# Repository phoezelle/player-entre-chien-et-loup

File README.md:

# player-entre-chien-et-loup
audio player for urban ballad http://www.cie-entrechienetloup.net/spectacles/verena-velvet.htm

The audio player work with 1 dedicated electronic card (cf pcb folder)
use atmega 328, vlsi vs1033/53, nordic NRF24L01+

You can control the system with a dedicated remote (cf pcb folder)
use atmega 328, hc595, nordic NRF24L01+, sparkfun LCD, keypad (optional)

use like arduino library
Player
Remote

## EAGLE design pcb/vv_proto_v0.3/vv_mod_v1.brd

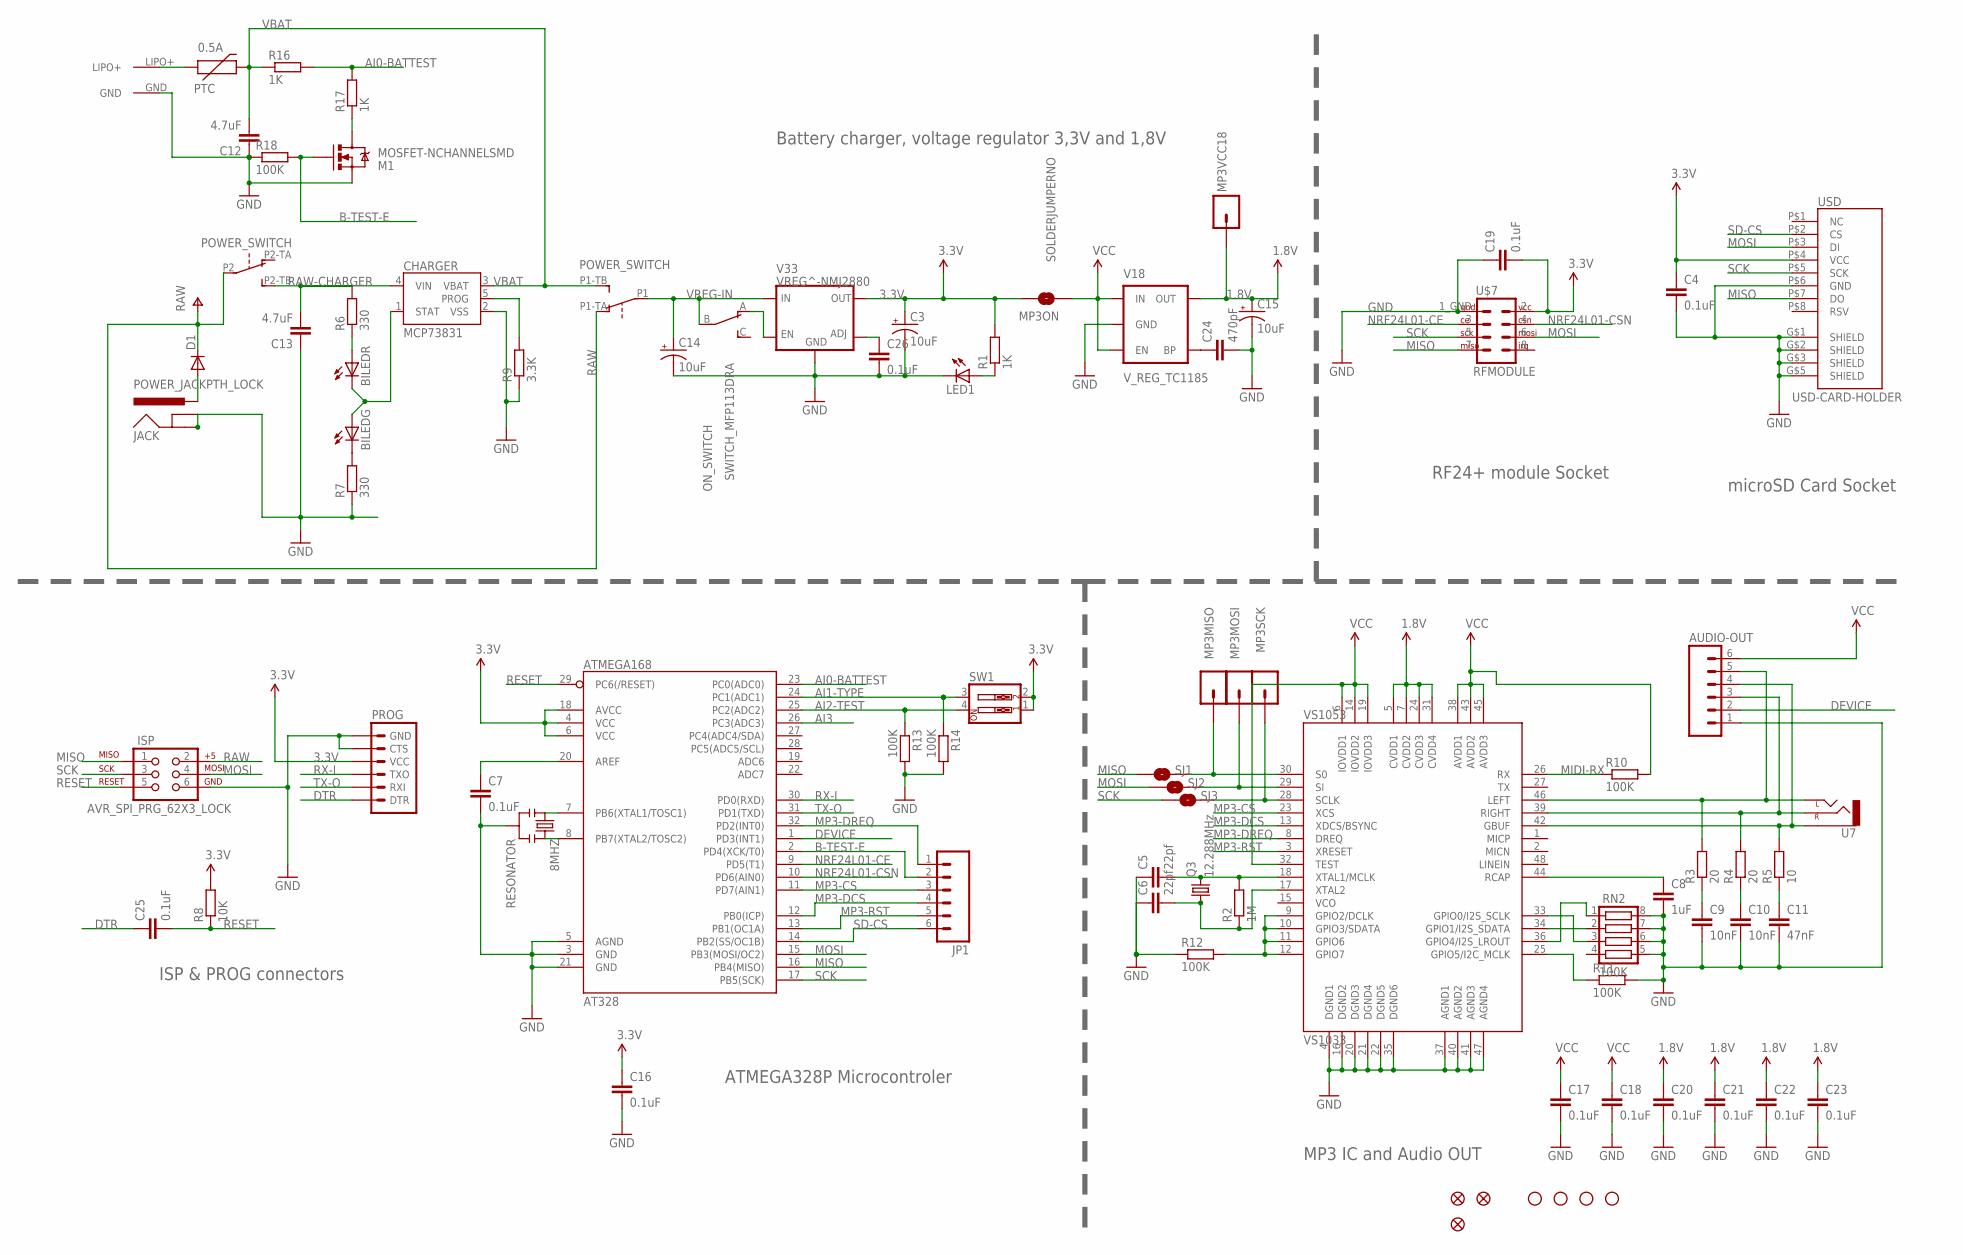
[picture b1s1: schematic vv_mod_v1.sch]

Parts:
0.5A: PTC; PTC-1210
8MHZ: RESONATOR; RESONATOR_7MM
AT328: ATMEGA168; TQFP32-08
AUDIO-OUT: M06LOCK; 1X06_LOCK
BILED: BILED; 2XLED
C3, C14, C15: 10uF; EIA3216
C4, C7, C16, C17, C18, C19, C20, C21, C22, C23, C25, C26: 0.1uF; C0805
C5, C6: 22pf; C0603
C8: 1uF; C0603
C9, C10: 10nF; C0603
C11: 47nF; C0603
C12, C13: 4.7uF; C0603
C24: 470pF; C0603
CHARGER: MCP73831; SOT23-5
D1: DIODESMA-KIT; SMA-DIODE-KIT
ISP: AVR_SPI_PRG_62X3_LOCK; 2X3_LOCK
JACK: POWER_JACKPTH_LOCK; POWER_JACK_PTH_LOCK
JP1: M06SIP; 1X06
JP2, JP3, JP8: FIDUCIAL1X2.5; FIDUCIAL-1X2.5
JP4, JP5, JP6, JP7: STAND-OFF
LED1: LED1206; LED-1206
M1: MOSFET-NCHANNELSMD; SOT23-3
MP3MISO, MP3MOSI, MP3SCK, MP3VCC18: M01SMD-4.5X1.5; PAD-1.5X4.5
MP3ON: SOLDERJUMPERNO; SJ_2S-NO
ON_SWITCH: SWITCH_MFP113DRA; SWITCH
POWER_SWITCH: JS202011SCQNPIN; SWITCHPOWER
PROG: ARDUINO_SERIAL_PROGRAMLOCK; 1X06_LOCK
Q3: 12.288MHz; HC49UP
R1, R16, R17: 1K; R0603
R2: 1M; R0603
R3, R4: 20; R0603
R5: 10; R0603
R6, R7: 330; R0805
R8: 10K; R0603
R9: 3.3K; R0603
R10, R11, R12, R13, R14, R18: 100K; R0805
RN2: 100K; CTS742C083
SJ1, SJ2, SJ3: SOLDERJUMPERNO; SJ_2S-NO
SW1: SW_DIP-2; DIPSWITCH-02
U7: AUDIO-JACKPTH; AUDIO-JACK
U$7: RFMODULE; 2X5_RFMODULE
U$8: LIPO_PAD; 2X1_LIPO_PAD
USD: USD-CARD-HOLDER; MICRO-SD-MOLEX-47579-001
V18: V_REG_TC1185; SOT23-5
V33: VREG^-NMJ2880; SOT-89
VS1053: VS1033; LQFP-48

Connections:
1.8V: C15.A (+), C20.1, C21.1, C22.1, C23.1, MP3VCC18.P$1, V18.5 (OUT), VS1053.5 (CVDD1), VS1053.7 (CVDD2), VS1053.24 (CVDD3), VS1053.31 (CVDD4)
3.3V: AT328.4 (VCC), AT328.6 (VCC), AT328.18 (AVCC), C3.A (+), C4.1, C16.1, C19.2, MP3ON.2, PROG.4 (VCC), R1.2, R8.2, SW1.1, SW1.2, U$7.2 (VCC), USD.P$4 (VCC), V33.4 (OUT)
100K-1: R12.2, VS1053.9 (GPIO2/DCLK), VS1053.10 (GPIO3/SDATA), VS1053.11 (GPIO6), VS1053.12 (GPIO7)
AI0-BATTEST: AT328.23 (PC0(ADC0)), R16.2, R17.2
AI1-TYPE: AT328.24 (PC1(ADC1)), R14.1, SW1.3
AI2-TEST: AT328.25 (PC2(ADC2)), R13.1, SW1.4
AI3: AT328.26 (PC3(ADC3))
AREF: AT328.20 (AREF), C7.1
B-TEST-E: AT328.2 (PD4(XCK/T0)), JP1.2, M1.1 (G), R18.2
DEVICE: AT328.1 (PD3(INT1)), AUDIO-OUT.2
DTR: C25.1, PROG.1 (DTR)
GBUF: AUDIO-OUT.4, R5.2, U7.SLEEVE, VS1053.42 (GBUF)
GND: 8MHZ.2, AT328.3 (GND), AT328.5 (AGND), AT328.21 (GND), AUDIO-OUT.1, C3.C (-), C4.2, C5.1, C6.1, C7.2, C8.2, C9.2, C10.2, C11.2, C12.1, C13.1, C14.C (-), C15.C (-), C16.2, C17.2, C18.2, C19.1, C20.2, C21.2, C22.2, C23.2, C24.2, C26.2, CHARGER.2 (VSS), ISP.6, JACK.GND, JACK.GNDBREAK, LED1.C, M1.2 (S), PROG.5 (CTS), PROG.6 (GND), R7.1, R9.1, R11.2, R12.1, R13.2, R14.2, R18.1, RN2.5, RN2.6, RN2.7, RN2.8, U$7.1_GND (GND), U$8.GND, USD.G$1 (SHIELD), USD.G$2 (SHIELD), USD.G$3 (SHIELD), USD.G$5 (SHIELD), USD.P$6 (GND), V18.2 (GND), V33.2 (GND), VS1053.4 (DGND1), VS1053.16 (DGND2), VS1053.20 (DGND3), VS1053.21 (DGND4), VS1053.22 (DGND5), VS1053.35 (DGND6), VS1053.37 (AGND1), VS1053.40 (AGND2), VS1053.41 (AGND3), VS1053.47 (AGND4)
LEFT: AUDIO-OUT.5, R3.2, U7.TIP (LEFT), VS1053.46 (LEFT)
MIDI-RX: R10.1, VS1053.26 (RX)
MISO: AT328.16 (PB4(MISO)), ISP.1, SJ1.1, U$7.7 (MISO), USD.P$7 (DO)
MISOMP3: MP3MISO.P$1, SJ1.2, VS1053.30 (S0)
MOSI: AT328.15 (PB3(MOSI/OC2)), ISP.4, SJ2.1, U$7.6 (MOSI), USD.P$3 (DI)
MOSIMP3: MP3MOSI.P$1, SJ2.2, VS1053.29 (SI)
MP3-CS: AT328.11 (PD7(AIN1)), JP1.3, VS1053.23 (XCS)
MP3-DCS: AT328.12 (PB0(ICP)), JP1.4, VS1053.13 (XDCS/BSYNC)
MP3-DREQ: AT328.32 (PD2(INT0)), JP1.1, VS1053.8 (DREQ)
MP3-RST: AT328.13 (PB1(OC1A)), JP1.5, VS1053.3 (XRESET)
unnamed: ON_SWITCH.A (O), V33.1 (EN)
unnamed: C26.1, V33.3 (ADJ)
unnamed: RN2.1, VS1053.36 (GPIO4/I2S_LROUT)
unnamed: LED1.A, R1.1
unnamed: RN2.3, VS1053.33 (GPIO0/I2S_SCLK)
unnamed: R11.1, VS1053.25 (GPIO5/I2C_MCLK)
unnamed: 8MHZ.1, AT328.7 (PB6(XTAL1/TOSC1))
unnamed: 8MHZ.3, AT328.8 (PB7(XTAL2/TOSC2))
unnamed: RN2.2, VS1053.34 (GPIO1/I2S_SDATA)
unnamed: D1.A, JACK.PWR
unnamed: C9.1, R3.1
unnamed: C10.1, R4.1
unnamed: C11.1, R5.1
unnamed: BILED.A2 (A), R6.1
unnamed: BILED.C3 (C), R7.2
unnamed: CHARGER.5 (PROG), R9.2
unnamed: M1.3 (D), R17.1
unnamed: C24.1, V18.4 (BP)
NRF24L01-CE: AT328.9 (PD5(T1)), U$7.3 (CE)
NRF24L01-CSN: AT328.10 (PD6(AIN0)), U$7.4 (CSN)
RAW: D1.C, ISP.2, POWER_SWITCH.P1-TA (O), POWER_SWITCH.P2
RAW-CHARGER: C13.2, CHARGER.4 (VIN), POWER_SWITCH.P2-TB (S), R6.2
RCAP: C8.1, VS1053.44 (RCAP)
RESET: AT328.29 (PC6(/RESET)), C25.2, ISP.5, R8.1
RIGHT: AUDIO-OUT.3, R4.2, U7.RING (RIGHT), VS1053.39 (RIGHT)
RX-I: AT328.30 (PD0(RXD)), PROG.3 (TXO)
SCK: AT328.17 (PB5(SCK)), ISP.3, SJ3.1, U$7.5 (SCK), USD.P$5 (SCK)
SCKMP3: MP3SCK.P$1, SJ3.2, VS1053.28 (SCLK)
SD-CS: AT328.14 (PB2(SS/OC1B)), JP1.6, USD.P$2 (CS)
STAT: BILED.A1 (A), BILED.C4 (C), CHARGER.1 (STAT)
TX-O: AT328.31 (PD1(TXD)), PROG.2 (RXI)
VBAT: 0.5A.2, C12.2, CHARGER.3 (VBAT), POWER_SWITCH.P1-TB (S), R16.1
VBAT-RAW: 0.5A.1, U$8.LIPO+
VCC: AUDIO-OUT.6, C17.1, C18.1, MP3ON.1, R10.2, V18.1 (IN), V18.3 (EN), VS1053.6 (IOVDD1), VS1053.14 (IOVDD2), VS1053.19 (IOVDD3), VS1053.32 (TEST), VS1053.38 (AVDD1), VS1053.43 (AVDD2), VS1053.45 (AVDD3)
VREG-IN: C14.A (+), ON_SWITCH.B, POWER_SWITCH.P1, V33.5 (IN)
XTAL1_MP3: C5.2, Q3.2, R2.2, VS1053.18 (XTAL1/MCLK)
XTAL2_MP3: C6.2, Q3.1, R2.1, VS1053.17 (XTAL2)

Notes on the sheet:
ISP & PROG connectors
MP3 IC and Audio OUT
microSD Card Socket
RF24+ module Socket
Battery charger, voltage regulator 3,3V and 1,8V
ATMEGA328P Microcontroler

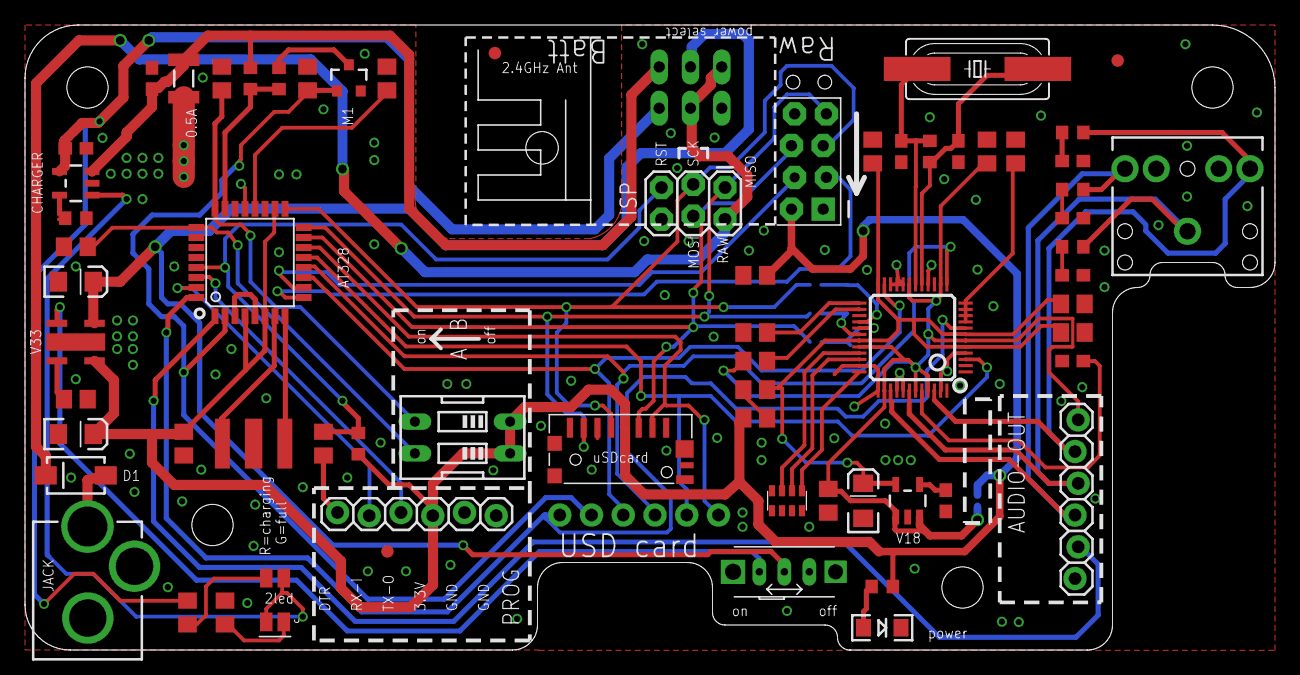
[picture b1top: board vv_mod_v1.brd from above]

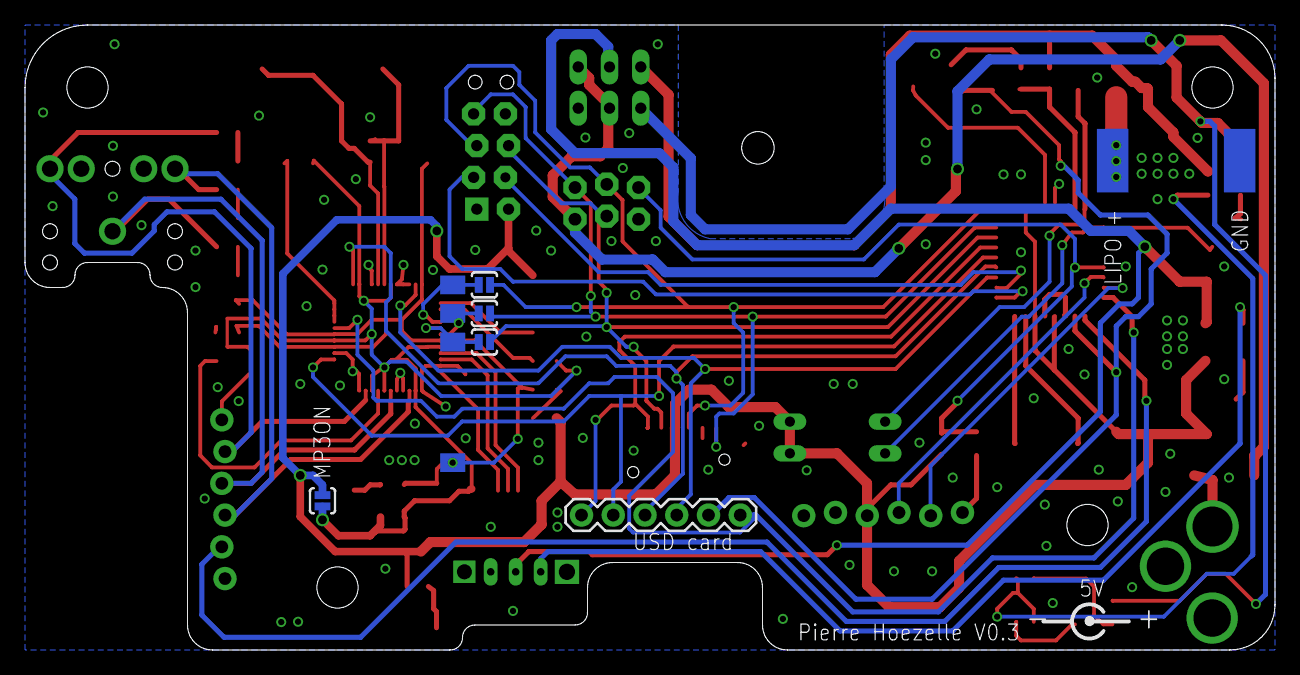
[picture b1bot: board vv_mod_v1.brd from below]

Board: 2 copper layers, 100.0 x 50.0 mm, 81 parts (9 on the bottom side), 59 nets.

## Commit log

2016-01-05 initial commit to share project
2016-01-09 update notice v2
2016-01-09 update noticev2
2016-04-24 better restart for borne + more ID safety
